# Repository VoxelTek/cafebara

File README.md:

# Stormbreaker
### A ripoff of YveltalGriffin's Mjolnir

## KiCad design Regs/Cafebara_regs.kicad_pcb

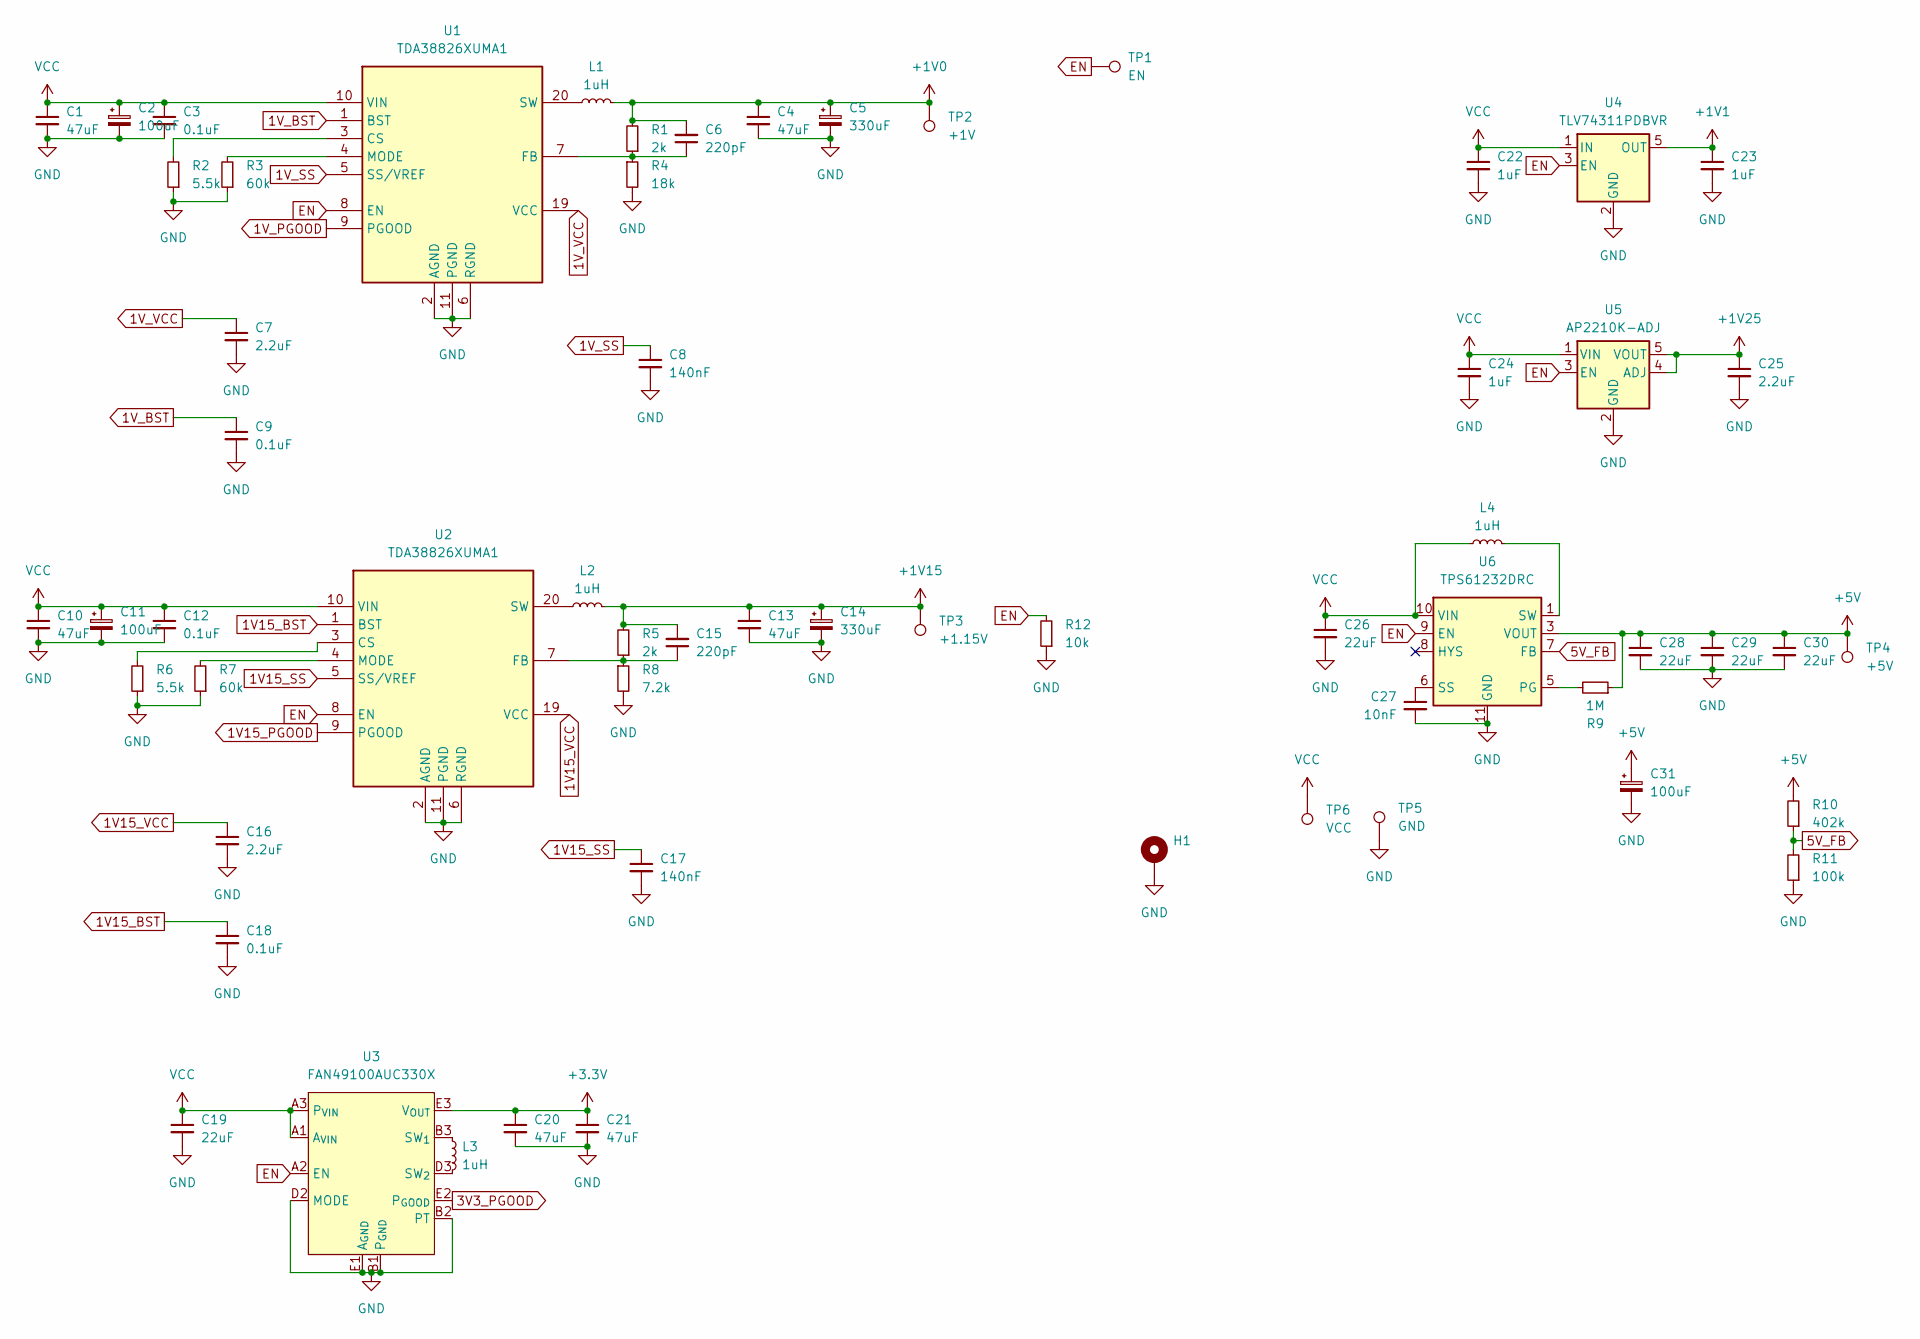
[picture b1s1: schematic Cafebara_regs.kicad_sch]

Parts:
C1, C10: 47uF; C_0603_1608Metric
C2, C11, C31: 100uF; CP_EIA-3216-10_Kemet-I
C3, C9, C12, C18: 0.1uF; C_0402_1005Metric
C4, C13, C20, C21: 47uF; C_0805_2012Metric
C5, C14: 330uF; CP_EIA-3528-15_AVX-H
C6, C15: 220pF; C_0402_1005Metric
C7, C16, C25: 2.2uF; C_0603_1608Metric
C8, C17: 140nF; C_0402_1005Metric
C19, C26: 22uF; C_0805_2012Metric
C22, C23, C24: 1uF; C_0603_1608Metric
C27: 10nF; C_0402_1005Metric
C28, C29, C30: 22uF; C_0603_1608Metric
H1: MountingHole_2.2mm_M2_Pad_Via
L1, L2, L4: 1uH; L_Sunlord_MWSA0624S
L3: 1uH; L_Murata_DFE201610P
R1, R5: 2k; R_0402_1005Metric
R2, R6: 5.5k; R_0402_1005Metric
R3, R7: 60k; R_0402_1005Metric
R4: 18k; R_0402_1005Metric
R8: 7.2k; R_0402_1005Metric
R9: 1M; R_0402_1005Metric
R10: 402k; R_0402_1005Metric
R11: 100k; R_0402_1005Metric
R12: 10k; R_0402_1005Metric
TP1: EN; TestPoint_Pad_D1.5mm
TP2: +1V; TestPoint_THTPad_D2.5mm_Drill1.2mm
TP3: +1.15V; TestPoint_THTPad_D2.5mm_Drill1.2mm
TP4: +5V; TestPoint_THTPad_D2.5mm_Drill1.2mm
TP5: GND; TestPoint_THTPad_D2.5mm_Drill1.2mm
TP6: VCC; TestPoint_THTPad_D2.5mm_Drill1.2mm
U1, U2: TDA38826XUMA1; Manufacturer_Part_Number TDA38826XUMA1
U3: FAN49100AUC330X; WLCSP-20_1.994x1.94mm_Layout4x5_P0.4mm
U4: TLV74311PDBVR; SOT-23-5
U5: AP2210K-ADJ; SOT-23-5
U6: TPS61232DRC; Texas_S-PVSON-N10_ThermalVias

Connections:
1V15_BST: C18.1, U2.1 (BST)
1V15_PGOOD: U2.9 (PGOOD)
1V15_SS: C17.1, U2.5 (SS/VREF)
1V15_VCC: C16.1, U2.19 (VCC)
1V_BST: C9.1, U1.1 (BST)
1V_PGOOD: U1.9 (PGOOD)
1V_SS: C8.1, U1.5 (SS/VREF)
1V_VCC: C7.1, U1.19 (VCC)
3V3_PGOOD: U3.E2 (P_{GOOD})
5V_FB: R10.1, R11.2, U6.7 (FB)
+1V0: C4.1, C5.1, C6.2, L1.2, R1.2, TP2.1
+1V1: C23.1, U4.5 (OUT)
+1V15: C13.1, C14.1, C15.2, L2.2, R5.2, TP3.1
+1V25: C25.1, U5.4 (ADJ), U5.5 (VOUT)
+3.3V: C20.1, C21.1, U3.E3 (V_{OUT}), U3.E4 (V_{OUT})
+5V: C28.1, C29.1, C30.1, C31.1, R9.1, R10.2, TP4.1, U6.3 (VOUT), U6.4 (VOUT)
EN: R12.2, TP1.1, U1.8 (EN), U2.8 (EN), U3.A2 (EN), U4.3 (EN), U5.3 (EN), U6.9 (EN)
GND: C1.2, C2.2, C3.2, C4.2, C5.2, C7.2, C8.2, C9.2, C10.2, C11.2, C12.2, C13.2, C14.2, C16.2, C17.2, C18.2, C19.2, C20.2, C21.2, C22.2, C23.2, C24.2, C25.2, C26.2, C27.2, C28.2, C29.2, C30.2, C31.2, H1.1, R2.1, R3.1, R4.2, R6.1, R7.1, R8.2, R11.1, R12.1, TP5.1, U1.2 (AGND), U1.6 (RGND), U1.11 (PGND), U1.12 (PGND), U1.13 (PGND), U1.14 (PGND), U1.15 (PGND), U1.16 (PGND), U1.17 (PGND), U1.18 (PGND), U1.22 (PGND), U2.2 (AGND), U2.6 (RGND), U2.11 (PGND), U2.12 (PGND), U2.13 (PGND), U2.14 (PGND), U2.15 (PGND), U2.16 (PGND), U2.17 (PGND), U2.18 (PGND), U2.22 (PGND), U3.B1 (P_{GND}), U3.B2 (PT), U3.C1 (P_{GND}), U3.C2 (P_{GND}), U3.C3 (P_{GND}), U3.C4 (P_{GND}), U3.D1 (P_{GND}), U3.D2 (MODE), U3.E1 (A_{GND}), U4.2 (GND), U5.2 (GND), U6.11 (GND)
unnamed: L3.1, U3.B3 (SW_{1}), U3.B4 (SW_{1})
unnamed: L3.2, U3.D3 (SW_{2}), U3.D4 (SW_{2})
unnamed: L4.2, U6.1 (SW), U6.2 (SW)
unnamed: R2.2, U1.3 (CS)
unnamed: C6.1, R1.1, R4.1, U1.7 (FB)
unnamed: R3.2, U1.4 (MODE)
unnamed: L1.1, U1.20 (SW)
unnamed: R6.2, U2.3 (CS)
unnamed: C15.1, R5.1, R8.1, U2.7 (FB)
unnamed: R7.2, U2.4 (MODE)
unnamed: L2.1, U2.20 (SW)
unnamed: R9.2, U6.5 (PG)
unnamed: C27.1, U6.6 (SS)
VCC: C1.1, C2.1, C3.1, C10.1, C11.1, C12.1, C19.1, C22.1, C24.1, C26.1, L4.1, TP6.1, U1.10 (VIN), U1.21 (VIN), U2.10 (VIN), U2.21 (VIN), U3.A1 (A_{VIN}), U3.A3 (P_{VIN}), U3.A4 (P_{VIN}), U4.1 (IN), U5.1 (VIN), U6.10 (VIN)

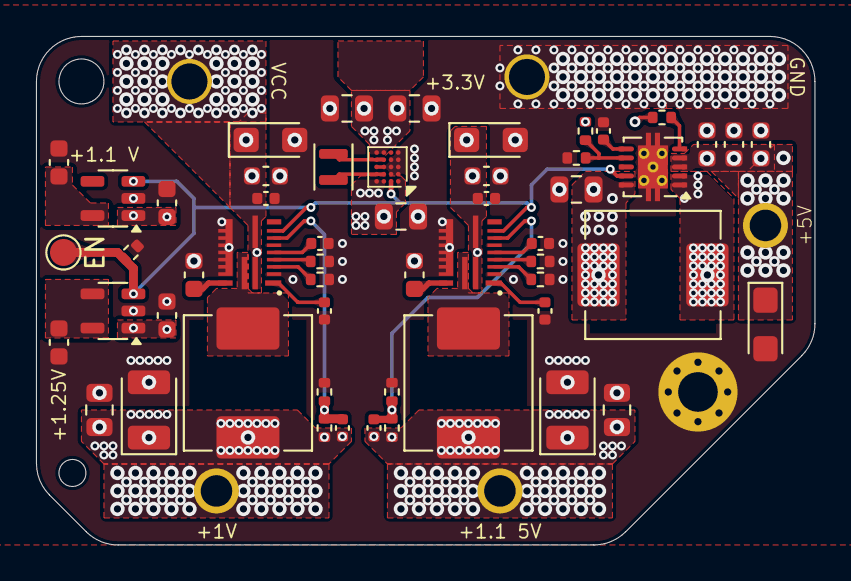
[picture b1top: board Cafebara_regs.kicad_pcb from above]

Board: 4 copper layers, 43.2 x 28.2 mm, 60 parts (0 on the bottom side), 29 nets.

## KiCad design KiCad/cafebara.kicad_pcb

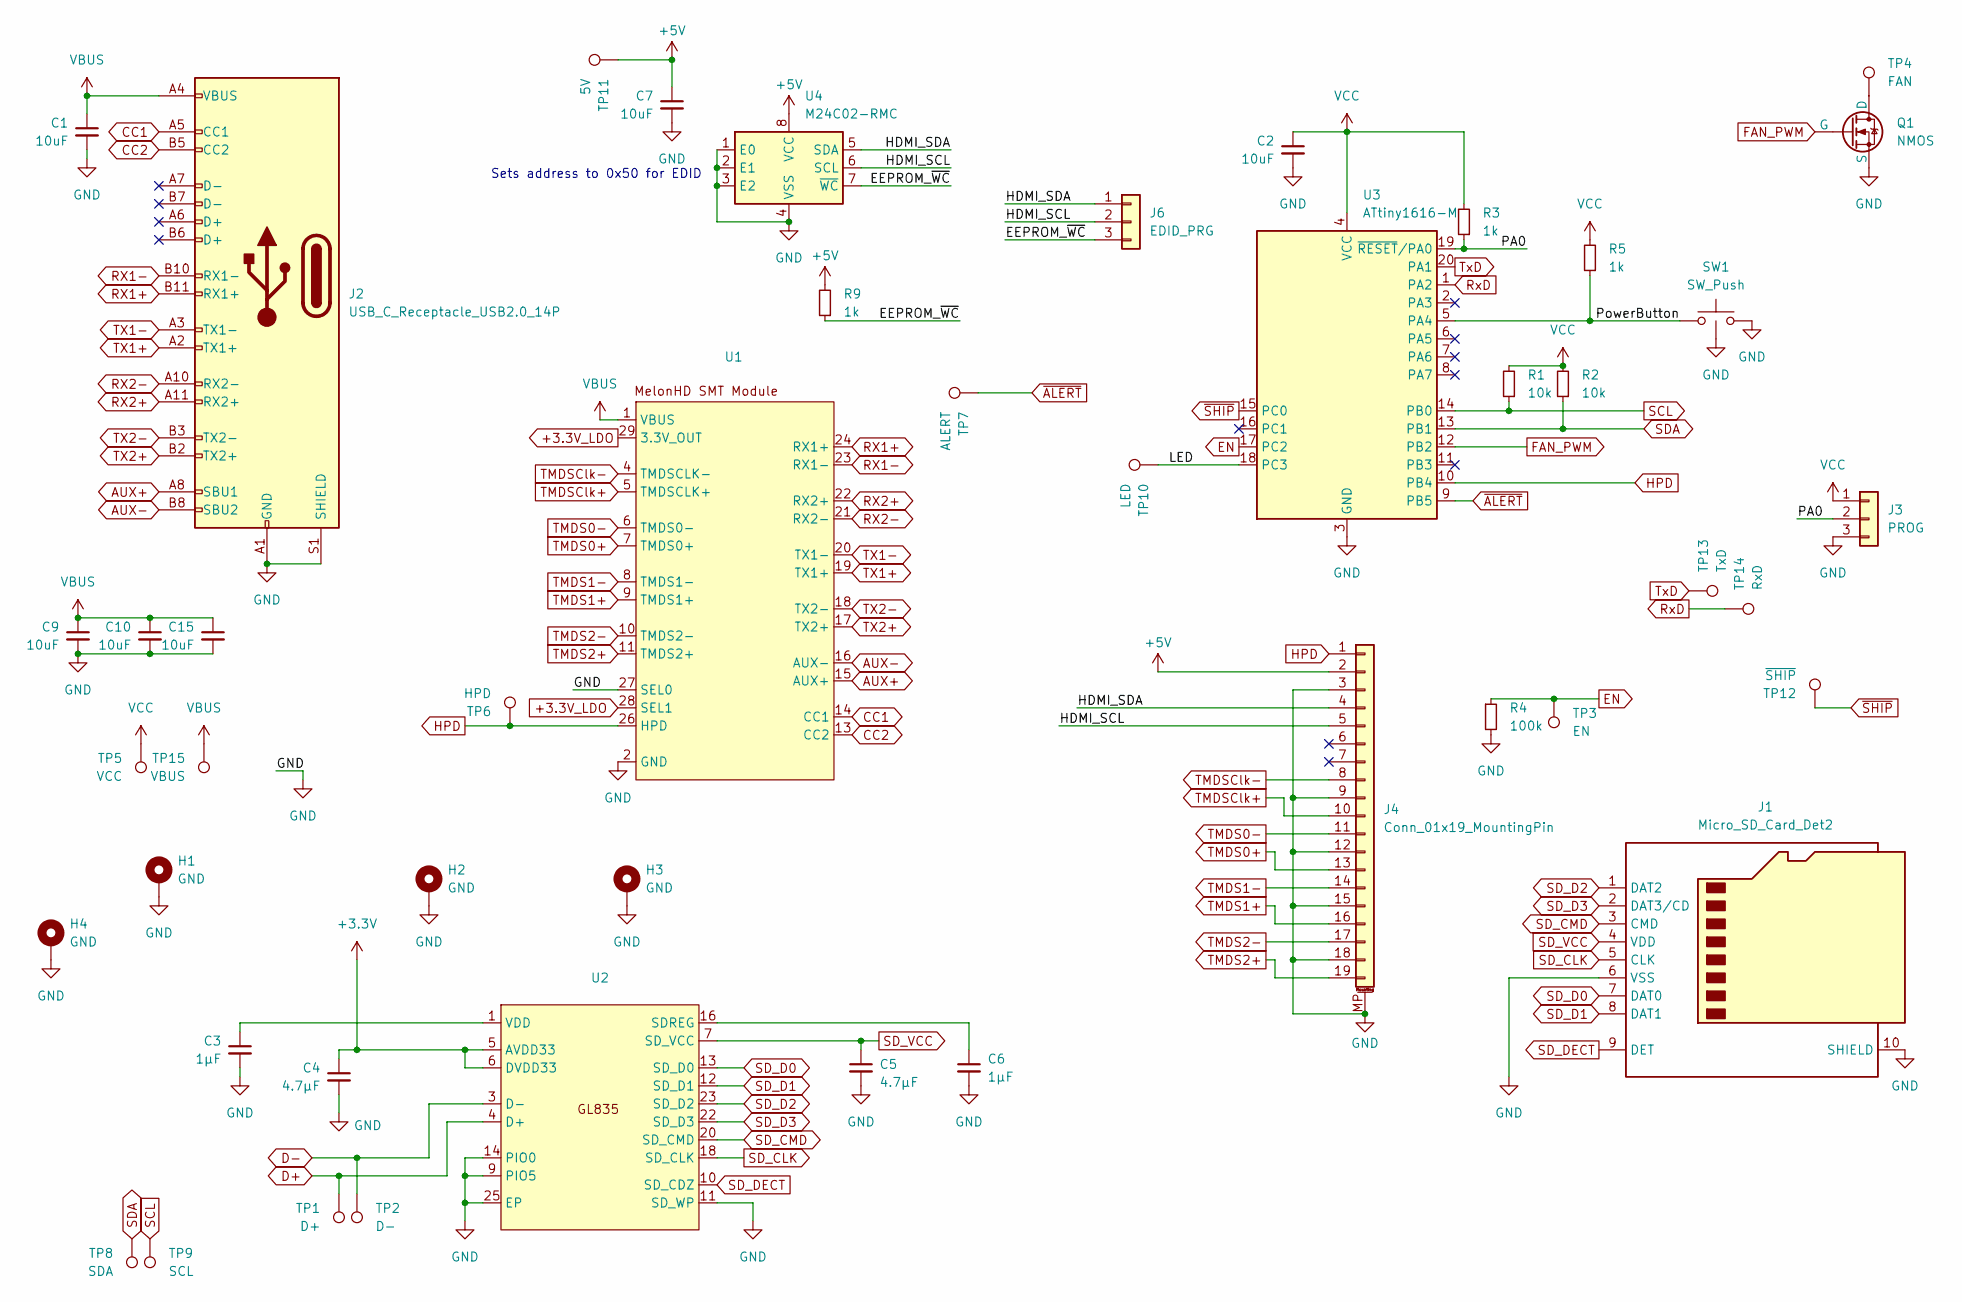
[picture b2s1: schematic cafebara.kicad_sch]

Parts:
C1: 10uF; C_0805_2012Metric
C2: 10uF; C_0402_1005Metric
C3, C6: 1μF; C_0402_1005Metric
C4: 4.7μF; C_0402_1005Metric
C5: 4.7μF; C_0603_1608Metric
C7, C9, C10, C15: 10uF; C_0603_1608Metric
H1, H2, H3, H4: GND; TestPoint_Plated_Hole_D2.0mm
J1: Micro_SD_Card_Det2; microSD_HC_Hirose_DM3D-SF
J2: USB_C_Receptacle_USB2.0_14P; GCT_USB4080-03-A_REVA1
J3: PROG; UPDI Pads
J4: Conn_01x19_MountingPin; TE_1-1734839-9_1x19-1MP_P0.5mm_Horizontal
J6: EDID_PRG; UPDI Pads
Q1: NMOS; SOT-523
R1, R2: 10k; R_0402_1005Metric
R3, R5, R9: 1k; R_0402_1005Metric
R4: 100k; R_0402_1005Metric
SW1: SW_Push; SW_Tactile_SPST_Angled_PTS645Vx58-2LFS
TP1: D+; TestPoint_Hole_D1.5mm_Small
TP2: D-; TestPoint_Hole_D1.5mm_Small
TP3: EN; TestPoint_Pad_D1.0mm_Small
TP4: FAN; TestPoint_Pad_D1.5mm
TP5: VCC; TestPoint_Plated_Hole_D2.0mm
TP6: HPD; TestPoint_Pad_D1.5mm
TP7: ALERT; TestPoint_Pad_D1.0mm_Small
TP8: SDA; TestPoint_Hole_D1.5mm_Small
TP9: SCL; TestPoint_Hole_D1.5mm_Small
TP10: LED; TestPoint_Pad_D1.0mm_Small
TP11: 5V; TestPoint_Pad_D1.5mm
TP12: ~{SHIP}; TestPoint_Pad_D1.0mm_Small
TP13: TxD; TestPoint_Pad_D1.0mm_Small
TP14: RxD; TestPoint_Pad_D1.0mm_Small
TP15: VBUS; TestPoint_Plated_Hole_D2.0mm
U1: melonHD_SMT
U2: HVQFN-24-1EP_4x4mm_P0.5mm_EP2.5x2.5mm
U3: ATtiny1616-M; VQFN-20-1EP_3x3mm_P0.4mm_EP1.7x1.7mm
U4: M24C02-RMC; UFDFPN_RMC

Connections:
+3.3V: C4.1, U2.5 (AVDD33), U2.6 (DVDD33)
+3.3V_LDO: U1.28 (SEL1), U1.29 (3.3V_OUT)
+5V: C7.1, J4.2, R9.2, TP11.1, U4.8 (VCC)
/EEPROM_~WC: J6.3, R9.1, U4.7 (~WC)
/HDMI_SCL: J4.5, J6.2, U4.6 (SCL)
/HDMI_SDA: J4.4, J6.1, U4.5 (SDA)
/LED: TP10.1, U3.18 (PC3)
/PA0: J3.2, R3.1, U3.19 (~RESET/PA0)
/PowerButton: R5.1, SW1.1, U3.5 (PA4)
AUX+: J2.A8 (SBU1), U1.15 (AUX+)
AUX-: J2.B8 (SBU2), U1.16 (AUX-)
CC1: J2.A5 (CC1), U1.14 (CC1)
CC2: J2.B5 (CC2), U1.13 (CC2)
D+: TP1.1, U2.4 (D+)
D-: TP2.1, U2.3 (D-)
EN: R4.1, TP3.1, U3.17 (PC2)
FAN_PWM: Q1.1 (G), U3.12 (PB2)
GND: C1.2, C2.2, C3.2, C4.2, C5.2, C6.2, C7.2, C9.2, C10.2, C15.2, H1.1, H2.1, H3.1, H4.1, J1.6 (VSS), J1.10 (SHIELD), J1.11 (SHIELD), J2.A1 (GND), J2.A12 (GND), J2.B1 (GND), J2.B12 (GND), J2.S1 (SHIELD), J3.3, J4.3, J4.9, J4.12, J4.15, J4.18, J4.MP (MountPin), Q1.2 (S), R4.2, SW1.2, SW1.MP, U1.2 (GND), U1.3 (GND), U1.12 (GND), U1.25 (GND), U1.27 (SEL0), U1.30 (GND), U1.31 (GND), U2.9 (PIO5), U2.11 (SD_WP), U2.14 (PIO0), U2.25 (EP), U3.3 (GND), U3.21 (GND), U4.1 (E0), U4.2 (E1), U4.3 (E2), U4.4 (VSS), U4.9 (VSS)
HPD: J4.1, TP6.1, U1.26 (HPD), U3.10 (PB4)
unnamed: Q1.3 (D), TP4.1
unnamed: C6.1, U2.16 (SDREG)
unnamed: C3.1, U2.1 (VDD)
RX1+: J2.B11 (RX1+), U1.24 (RX1+)
RX1-: J2.B10 (RX1-), U1.23 (RX1-)
RX2+: J2.A11 (RX2+), U1.22 (RX2+)
RX2-: J2.A10 (RX2-), U1.21 (RX2-)
RxD: TP14.1, U3.1 (PA2)
SCL: R1.1, TP9.1, U3.14 (PB0)
SDA: R2.1, TP8.1, U3.13 (PB1)
SD_CLK: J1.5 (CLK), U2.18 (SD_CLK)
SD_CMD: J1.3 (CMD), U2.20 (SD_CMD)
SD_D0: J1.7 (DAT0), U2.13 (SD_D0)
SD_D1: J1.8 (DAT1), U2.12 (SD_D1)
SD_D2: J1.1 (DAT2), U2.23 (SD_D2)
SD_D3: J1.2 (DAT3/CD), U2.22 (SD_D3)
SD_DECT: J1.9 (DET), U2.10 (SD_CDZ)
SD_VCC: C5.1, J1.4 (VDD), U2.7 (SD_VCC)
TMDS0+: J4.13, U1.7 (TMDS0+)
TMDS0-: J4.11, U1.6 (TMDS0-)
TMDS1+: J4.16, U1.9 (TMDS1+)
TMDS1-: J4.14, U1.8 (TMDS1-)
TMDS2+: J4.19, U1.11 (TMDS2+)
TMDS2-: J4.17, U1.10 (TMDS2-)
TMDSClk+: J4.10, U1.5 (TMDSCLK+)
TMDSClk-: J4.8, U1.4 (TMDSCLK-)
TX1+: J2.A2 (TX1+), U1.19 (TX1+)
TX1-: J2.A3 (TX1-), U1.20 (TX1-)
TX2+: J2.B2 (TX2+), U1.17 (TX2+)
TX2-: J2.B3 (TX2-), U1.18 (TX2-)
TxD: TP13.1, U3.20 (PA1)
VBUS: C1.1, C9.1, C10.1, C15.1, J2.A4 (VBUS), J2.A9 (VBUS), J2.B4 (VBUS), J2.B9 (VBUS), TP15.1, U1.1 (VBUS)
VCC: C2.1, J3.1, R1.2, R2.2, R3.2, R5.2, TP5.1, U3.4 (VCC)
~ALERT: TP7.1, U3.9 (PB5)
~SHIP: TP12.1, U3.15 (PC0)

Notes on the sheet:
Sets address to 0x50 for EDID

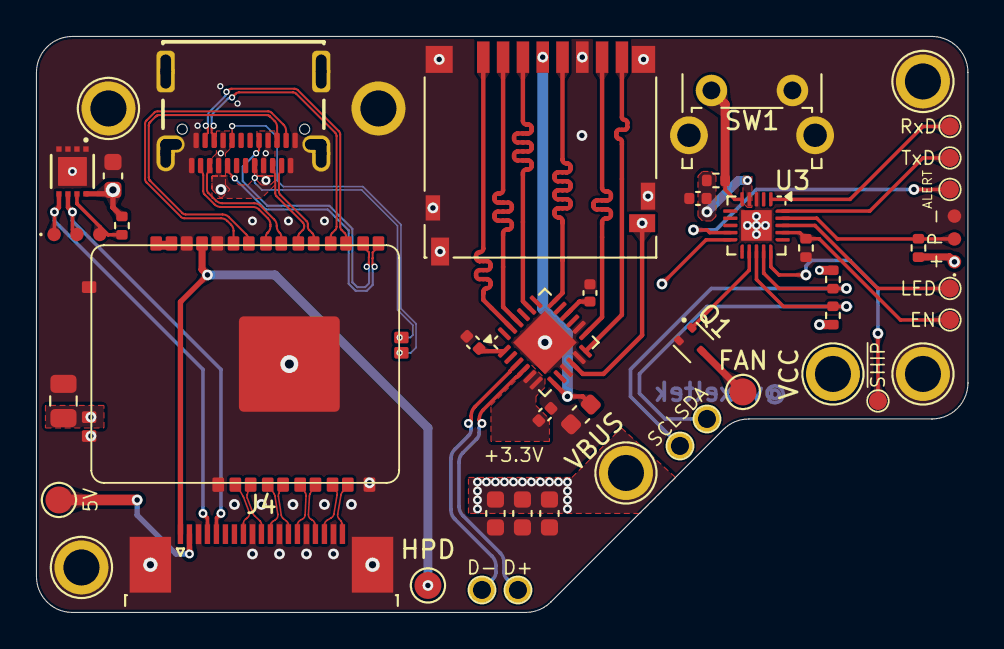
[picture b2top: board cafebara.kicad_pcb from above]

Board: 4 copper layers, 51.8 x 32.0 mm, 46 parts (0 on the bottom side), 54 nets.

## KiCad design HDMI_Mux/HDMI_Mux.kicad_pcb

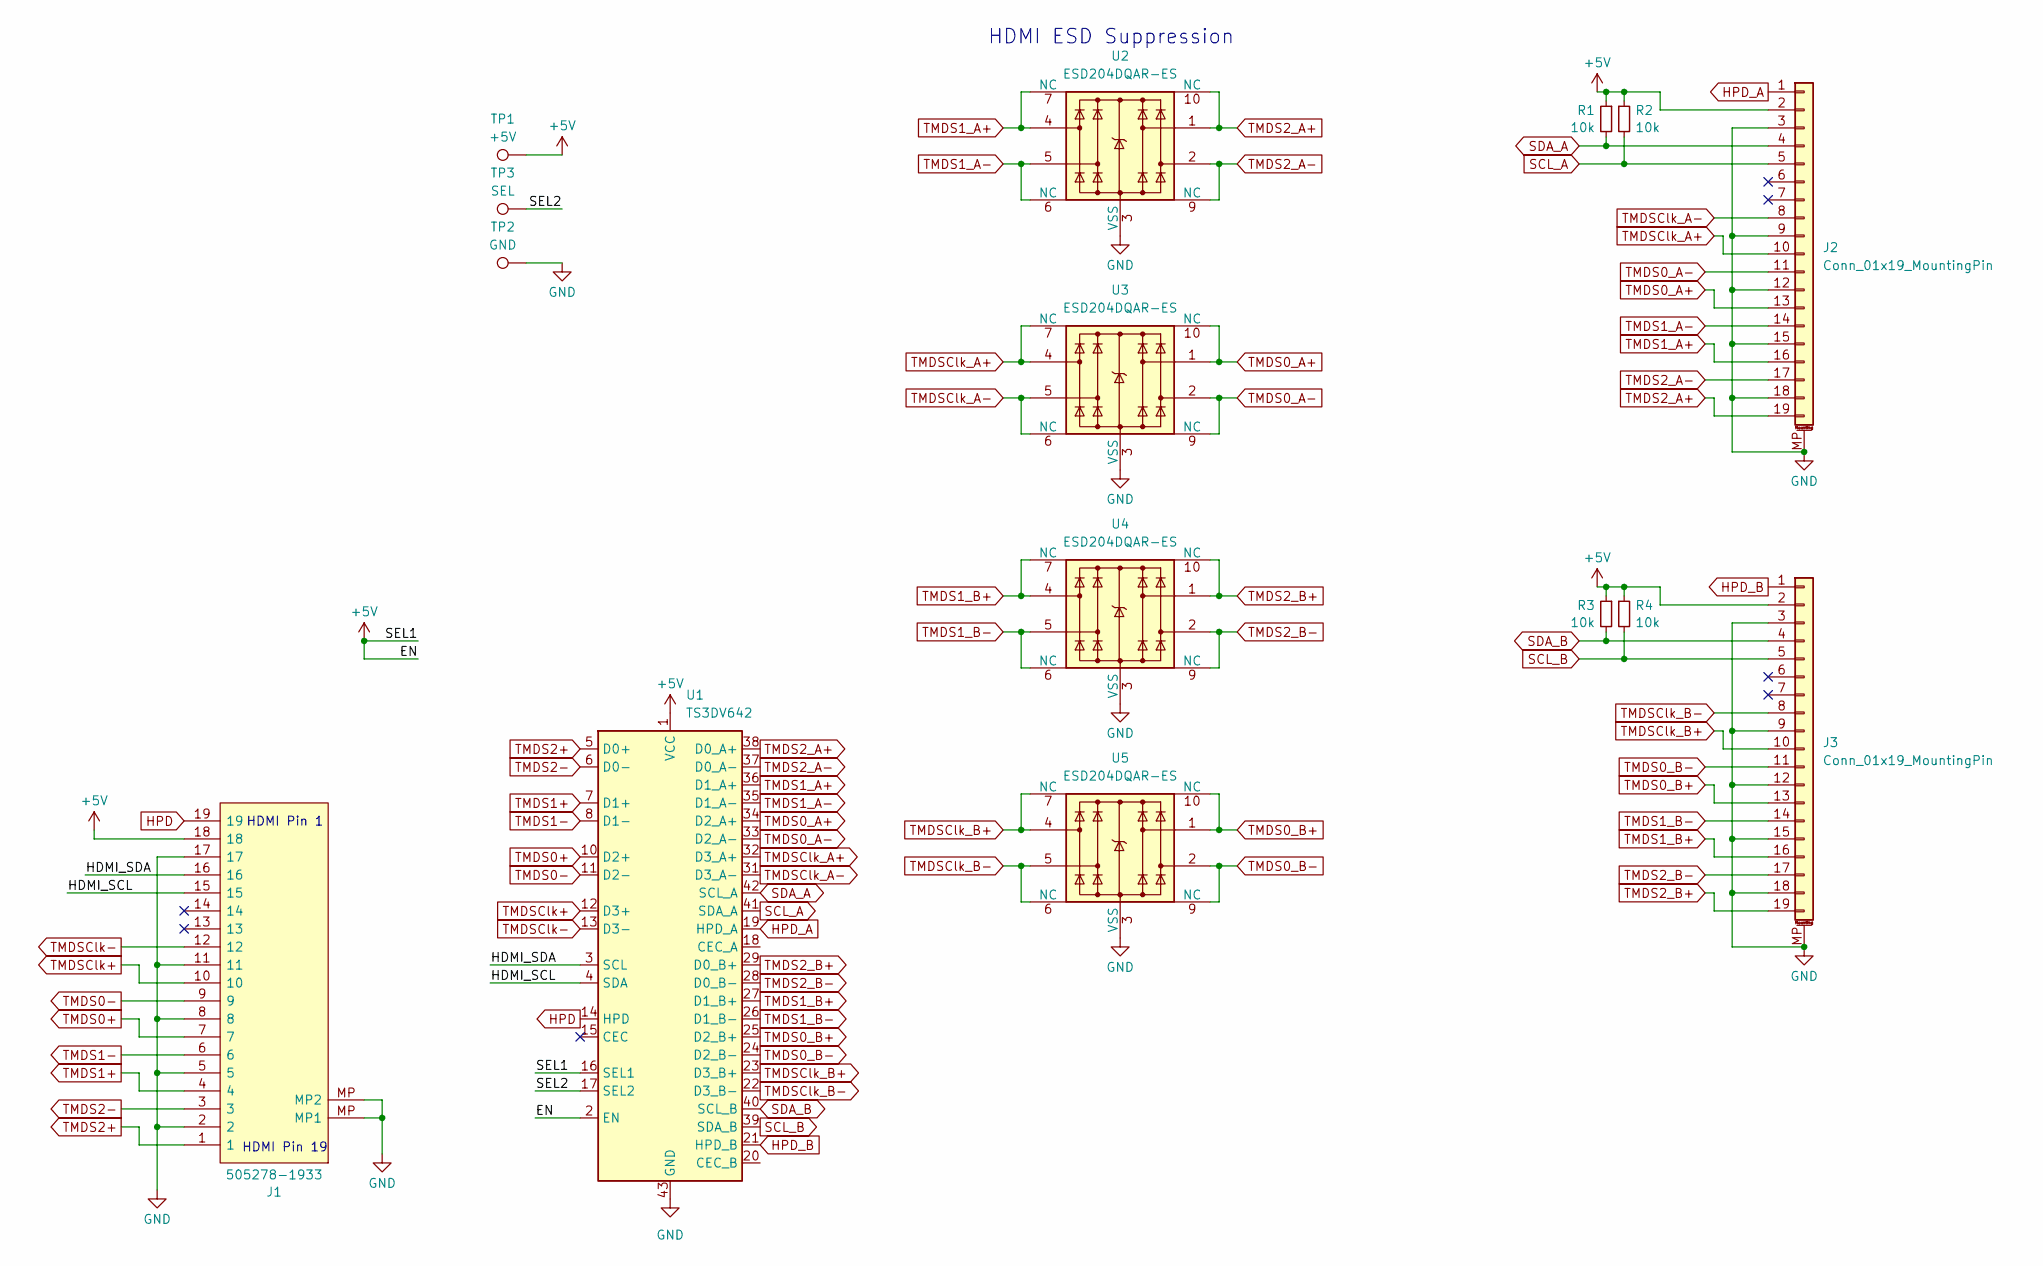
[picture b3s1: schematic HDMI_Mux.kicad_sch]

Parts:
J1: 505278-1933; Hirose_FH12-19S-0.5SH_1x19-1MP_P0.50mm_Horizontal; Mouser Part Number 538-505278-1933
J2, J3: Conn_01x19_MountingPin; Hirose_FH12-19S-0.5SH_1x19-1MP_P0.50mm_Horizontal
R1, R2, R3, R4: 10k; R_0402_1005Metric
TP1: +5V; TestPoint_Pad_D2.5mm
TP2: GND; TestPoint_Pad_D2.5mm
TP3: SEL; TestPoint_Pad_D1.5mm
U1: TS3DV642; WQFN-42-1EP_3.5x9mm_P0.5mm_EP2.05x7.55mm_ThermalVias
U2, U3, U4, U5: ESD204DQAR-ES; Diodes_UDFN-10_1.0x2.5mm_P0.5mm

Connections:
+5V: J1.18, J2.2, J3.2, R1.1, R2.1, R3.1, R4.1, TP1.1, U1.1 (VCC), U1.2 (EN), U1.16 (SEL1)
/HDMI_SCL: J1.15, U1.4 (SDA)
/HDMI_SDA: J1.16, U1.3 (SCL)
/SEL2: TP3.1, U1.17 (SEL2)
GND: J1.2, J1.5, J1.8, J1.11, J1.17, J1.MP (MP1), J2.3, J2.9, J2.12, J2.15, J2.18, J2.MP (MountPin), J3.3, J3.9, J3.12, J3.15, J3.18, J3.MP (MountPin), TP2.1, U1.43 (GND), U2.3 (VSS), U2.8 (VSS), U3.3 (VSS), U3.8 (VSS), U4.3 (VSS), U4.8 (VSS), U5.3 (VSS), U5.8 (VSS)
HPD: J1.19, U1.14 (HPD)
HPD_A: J2.1, U1.19 (HPD_A)
HPD_B: J3.1, U1.21 (HPD_B)
SCL_A: J2.5, R2.2, U1.41 (SDA_A)
SCL_B: J3.5, R4.2, U1.39 (SDA_B)
SDA_A: J2.4, R1.2, U1.42 (SCL_A)
SDA_B: J3.4, R3.2, U1.40 (SCL_B)
TMDS0+: J1.7, U1.10 (D2+)
TMDS0-: J1.9, U1.11 (D2-)
TMDS0_A+: J2.13, U1.34 (D2_A+), U3.1, U3.10 (NC)
TMDS0_A-: J2.11, U1.33 (D2_A-), U3.2, U3.9 (NC)
TMDS0_B+: J3.13, U1.25 (D2_B+), U5.1, U5.10 (NC)
TMDS0_B-: J3.11, U1.24 (D2_B-), U5.2, U5.9 (NC)
TMDS1+: J1.4, U1.7 (D1+)
TMDS1-: J1.6, U1.8 (D1-)
TMDS1_A+: J2.16, U1.36 (D1_A+), U2.4, U2.7 (NC)
TMDS1_A-: J2.14, U1.35 (D1_A-), U2.5, U2.6 (NC)
TMDS1_B+: J3.16, U1.27 (D1_B+), U4.4, U4.7 (NC)
TMDS1_B-: J3.14, U1.26 (D1_B-), U4.5, U4.6 (NC)
TMDS2+: J1.1, U1.5 (D0+)
TMDS2-: J1.3, U1.6 (D0-)
TMDS2_A+: J2.19, U1.38 (D0_A+), U2.1, U2.10 (NC)
TMDS2_A-: J2.17, U1.37 (D0_A-), U2.2, U2.9 (NC)
TMDS2_B+: J3.19, U1.29 (D0_B+), U4.1, U4.10 (NC)
TMDS2_B-: J3.17, U1.28 (D0_B-), U4.2, U4.9 (NC)
TMDSClk+: J1.10, U1.12 (D3+)
TMDSClk-: J1.12, U1.13 (D3-)
TMDSClk_A+: J2.10, U1.32 (D3_A+), U3.4, U3.7 (NC)
TMDSClk_A-: J2.8, U1.31 (D3_A-), U3.5, U3.6 (NC)
TMDSClk_B+: J3.10, U1.23 (D3_B+), U5.4, U5.7 (NC)
TMDSClk_B-: J3.8, U1.22 (D3_B-), U5.5, U5.6 (NC)

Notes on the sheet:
HDMI Pin 1
HDMI ESD Suppression
HDMI Pin 19

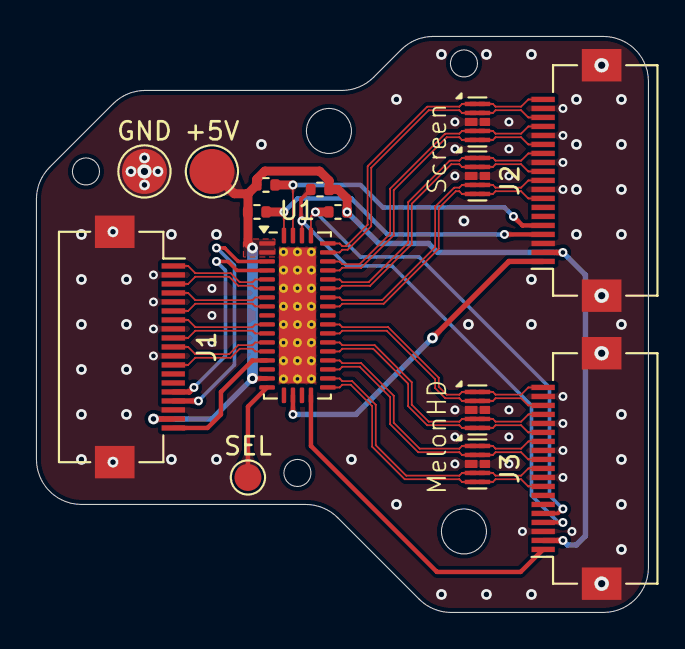
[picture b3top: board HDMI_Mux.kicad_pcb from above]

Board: 2 copper layers, 34.0 x 32.0 mm, 15 parts (0 on the bottom side), 36 nets.

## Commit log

2025-02-03 I am suffering
2025-02-04 aaaaaaaaa
2025-02-05 Stuff
2025-02-05 Misc suffering
2025-02-06 aaaaaaaaaaaa
2025-02-06 Mostly done, I think...?
2025-02-06 dimensions and other misc
2025-02-06 More updates
2025-02-07 created 3D model
2025-02-11 Cleanup, trace matching stuff...
2025-02-11 Simplifying, starting from scratch, removing melon
2025-02-11 more simplification
2025-02-11 3D models, some placements
2025-02-16 hhhhhhhhhh probably going to redesign again
2025-02-19 Have to rethink BQ placement
2025-02-19 Fix 3D, mostly finished I think
2025-02-19 Minor rearrangements
2025-02-20 Added fan and other batt, via stitched
2025-02-20 Minor track rearrangement
2025-02-20 More routing, via stitching, VCC zones
2025-02-23 more misc changes
2025-02-24 Add point for neopixel
2025-02-24 more minor misc modifications
2025-03-27 Redo power and BQ layout and routing
2025-03-27 Power and ground zones, gnd stitching
2025-03-28 Nearing completion...but no idea how to mount it
2025-03-31 Firmware development, minor hardware changes
2025-03-31 Add battery and power monitoring functions
2025-03-31 More LED code
2025-03-31 More LED code, minor board changes
2025-04-01 Adjust position of power pad
2025-04-01 Begin interface code, implement safety features
    Now loads (and writes) various settings from (and to) EEPROM. Added error handling, to an extent. Added comments for easier understanding. Emergency power-off and shipping mode in over-temp situation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
2025-04-01 Get first four bits of termCurrent
2025-04-01 Overtemp protection changes, I2C code fix
2025-04-01 More charging safety, other misc things
2025-04-01 Modify fan pin, implement fan control, misc
2025-04-01 Solder paste vectors, fix I2C error
2025-04-02 Write RVLoader code for Stormbreaker
    TODO: Modify the Lua code to support both boards, or even better, allow supporting indefinite boards
2025-04-02 Minor changes to code, for RVLoader integration
2025-04-02 Misc minor PCB modifications
2025-04-02 Add USB-C PD circuitry
2025-04-02 Adjustments to PD chip, WIP
2025-04-02 Teardropped pads, slight footprint adjustments
2025-04-02 Minor track changes
2025-04-03 Minor repositioning
2025-04-03 Minor changes
2025-04-04 Regenerate 3D model
2025-04-04 Button wait time change, other misc
2025-04-04 Touch-ups in preparation for ordering
2025-04-04 Gerber generation
2025-04-07 backup?
2025-04-07 Minor code changes
2025-04-10 Replace 0603 resistors with 0402s, generate BOM
2025-04-22 Misc positioning, add extra zone for batt
2025-04-26 Misc improvements
2025-04-29 Repositioning, moving things to front copper layer
2025-04-29 More repositioning and layout changes
2025-04-30 More misc improvements
2025-05-01 More more misc improvements
2025-05-01 Beginning to move husb to front of board
2025-05-06 Various misc changes
2025-05-07 Add BT enable pin
2025-05-07 Change BT to active high
2025-05-09 Add sleep functionality, remove BT enable pad
2025-05-09 Change programming "header"
2025-05-10 Minor code changes, minor PCB changes
2025-05-12 Minor firmware changes
2025-05-14 Misc changes
2025-05-14 Start work on Wii U version of Stormbreaker
2025-05-16 Lite version nearing completion
2025-05-18 TODO: MelonHD
2025-05-19 Begin melonHD integration
2025-05-23 integrate Wii U power regs
2025-05-25 Integrate core regs
2025-05-26 Add logo, other cool stuff
2025-05-27 Pretty much finished Capybara/cafebara
2025-05-27 Capybara init
2025-05-27 Rename project to "cafebara"
2025-05-27 Rename and merge
2025-05-27 Revert "Rename and merge"
    This reverts commit 31de9c7249c62d9b12a44b42921e26cd42b5dfd9.
2025-05-27 Rename project
2025-05-27 Misc placement and routing fixes
2025-09-09 Split regs into separate KiCad project
2025-09-09 Update firmware
2025-09-10 Largely finish positioning and routing
2025-09-10 Slight board outline adjustments
2025-09-10 Regulator board design finalisation
2025-09-11 Condense main cafebara board
2025-09-11 Begin work on HDMI mux board
2025-09-12 Finish HDMI mux, misc improvements to cafebara
2025-09-14 Minor misc updates
2025-09-15 Misc adjustments
2025-09-17 Misc changes to cafebara, add temperature board
2025-09-17 Add alert pin, EDID EEPROM, misc other changes
2025-09-17 Possibly planning to enlarge board...
2025-09-18 Expand board, add charge IC, other misc changes
2025-09-18 Misc minor board adjustments
2025-09-25 Misc
2025-10-10 Various improvements and misc changes
2025-10-13 Misc improvements, 3D model generation
2025-10-13 Several improvements
2025-10-14 Misc improvements to several boards
2025-10-14 Generate 3D, misc
2025-10-14 Split GND pad
2025-10-15 Other misc reg changes
2025-10-15 Misc improvements, firmware rewrite
2025-10-16 Rework, adding UART for Pi communication
2025-10-16 Begin change to new battery charge IC
    TODO:
    - complete transition
    - add battery protection
    - add fuel gauge?
2025-10-17 Began migration to 2S configuration
2025-10-17 Revert back to 1S configuration
2025-10-18 More misc progress
2025-11-01 More misc work
2025-11-08 More work for BMS portion
2026-04-21 Move to using 100W-Charging-PCB for battery charge
2026-06-07 misc changes and improvements
